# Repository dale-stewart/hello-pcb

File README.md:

# Hello PCB

A first PCB: a CR2032 coin cell lights a red LED while you hold down a pushbutton.
Designed in KiCad 10.

## Circuit

Pressing SW1 completes the loop from the cell through R1 and D1. With a 3 V cell and a red LED
dropping about 2 V, R1 limits the current to roughly 4–5 mA.

## Board

| | |
|---|---|
| Size | 34.0 × 32.4 mm, 4 mm corner radius |
| Layers | 2: tracks on top, GND fill on both sides, joined by 4 stitching vias |
| Mounting | 4 × M2 holes (2.2 mm, non-plated), 3 mm in from each corner (H1–H4) |
| Parts | All through-hole except the battery holder (surface mount) |

## Parts

| Ref | Part | Manufacturer | MPN | DigiKey | Mouser |
|---|---|---|---|---|---|
| BT1 | CR2032 holder | Keystone Electronics | 1058 | 36-1058-ND | 534-1058 |
| BT2 | CR2032 cell (not on board) | Panasonic | CR2032 | 11-CR2032-ND | 614-CR2032-200 ¹ |
| D1 | Red LED, 3 mm | Kingbright | WP710A10ID | 754-1606-ND | 604-WP710A10ID |
| R1 | 220 Ω, ¼ W, 1% | YAGEO | MFR-12FTF52-220R | 13-MFR-12FTF52-220RCT-ND | 603-MFR-12FTF52-220R |
| SW1 | 6 mm tactile switch, normally open | Aratas (formerly Omron) | B3F-1000 | SW400-ND | 653-B3F-1000 |

¹ The Mouser part is a Renata CR2032. Any CR2032 fits.

The parts for one board came to about $2.40 at either distributor in November 2026.

### Costed BOM

`tools/costed_bom.py` exports the BOM from the schematic and prices it with live DigiKey and
Mouser data:

```sh
python3 tools/costed_bom.py --boards 1,10
```

It writes `build/hello-pcb-bom.csv` and `build/hello-pcb-bom-costed.csv`. It needs API
credentials in `~/.config/distributor-api.env`:

```
MOUSER_API_KEY=...
DIGIKEY_CLIENT_ID=...
DIGIKEY_CLIENT_SECRET=...
```

The DigiKey credentials need a Production app subscribed to Product Information v4.

## Ordering boards

Upload `hello-pcb.kicad_pcb` directly to [OSH Park](https://oshpark.com/). No Gerber files are
needed, and a KiCad 10 file works. OSH Park doesn't refill the copper zones, so after editing
the board, press **B** in the PCB editor before saving.

## Files

| File | Contents |
|---|---|
| `hello-pcb.kicad_pro` | KiCad project |
| `hello-pcb.kicad_sch` | Schematic, with distributor part numbers on each symbol |
| `hello-pcb.kicad_pcb` | Board layout |
| `tools/costed_bom.py` | BOM export and live pricing script |
| `docs/` | Board renders for this README |
| `LICENSE` | CERN-OHL-P-2.0 licence text |

## License

This design is licensed under the
[CERN Open Hardware Licence Version 2 – Permissive](https://ohwr.org/cern_ohl_p_v2.txt)
(SPDX: `CERN-OHL-P-2.0`). You may use, modify, share and make boards from it, including
commercially. The full text is in [LICENSE](LICENSE).

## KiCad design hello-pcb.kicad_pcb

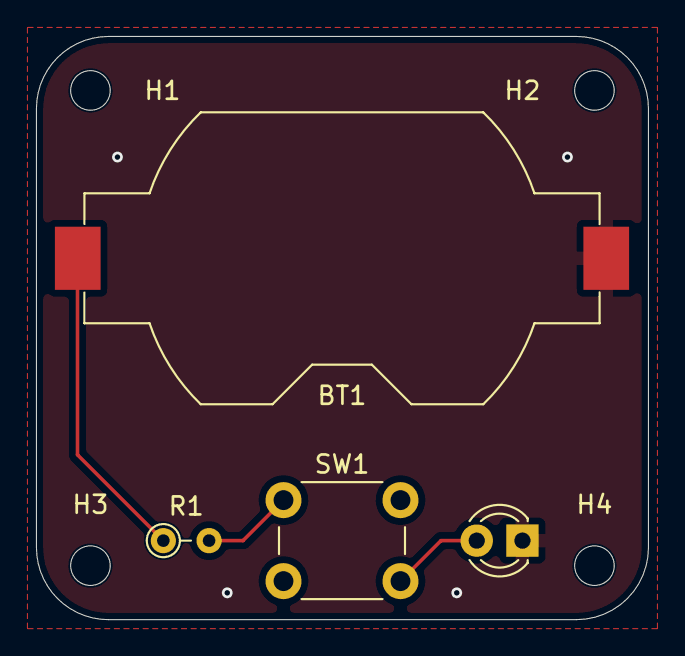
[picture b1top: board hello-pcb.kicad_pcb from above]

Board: 2 copper layers, 34.0 x 32.4 mm, 8 parts (0 on the bottom side), 4 nets.

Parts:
BT1: 3V; BatteryHolder_Keystone_1058_1x2032
D1: RED; LED_D3.0mm
H1: M2 top-left; MountingHole_2.2mm_M2
H2: M2 top-right; MountingHole_2.2mm_M2
H3: M2 bottom-left; MountingHole_2.2mm_M2
H4: M2 bottom-right; MountingHole_2.2mm_M2
R1: 220R; R_Axial_DIN0204_L3.6mm_D1.6mm_P2.54mm_Vertical
SW1: Pushbutton; SW_PUSH_6mm

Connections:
+3V: BT1.1 (+), R1.1
GND: BT1.2 (-), D1.1 (K)
unnamed: D1.2 (A), SW1.2
unnamed: R1.2, SW1.1
